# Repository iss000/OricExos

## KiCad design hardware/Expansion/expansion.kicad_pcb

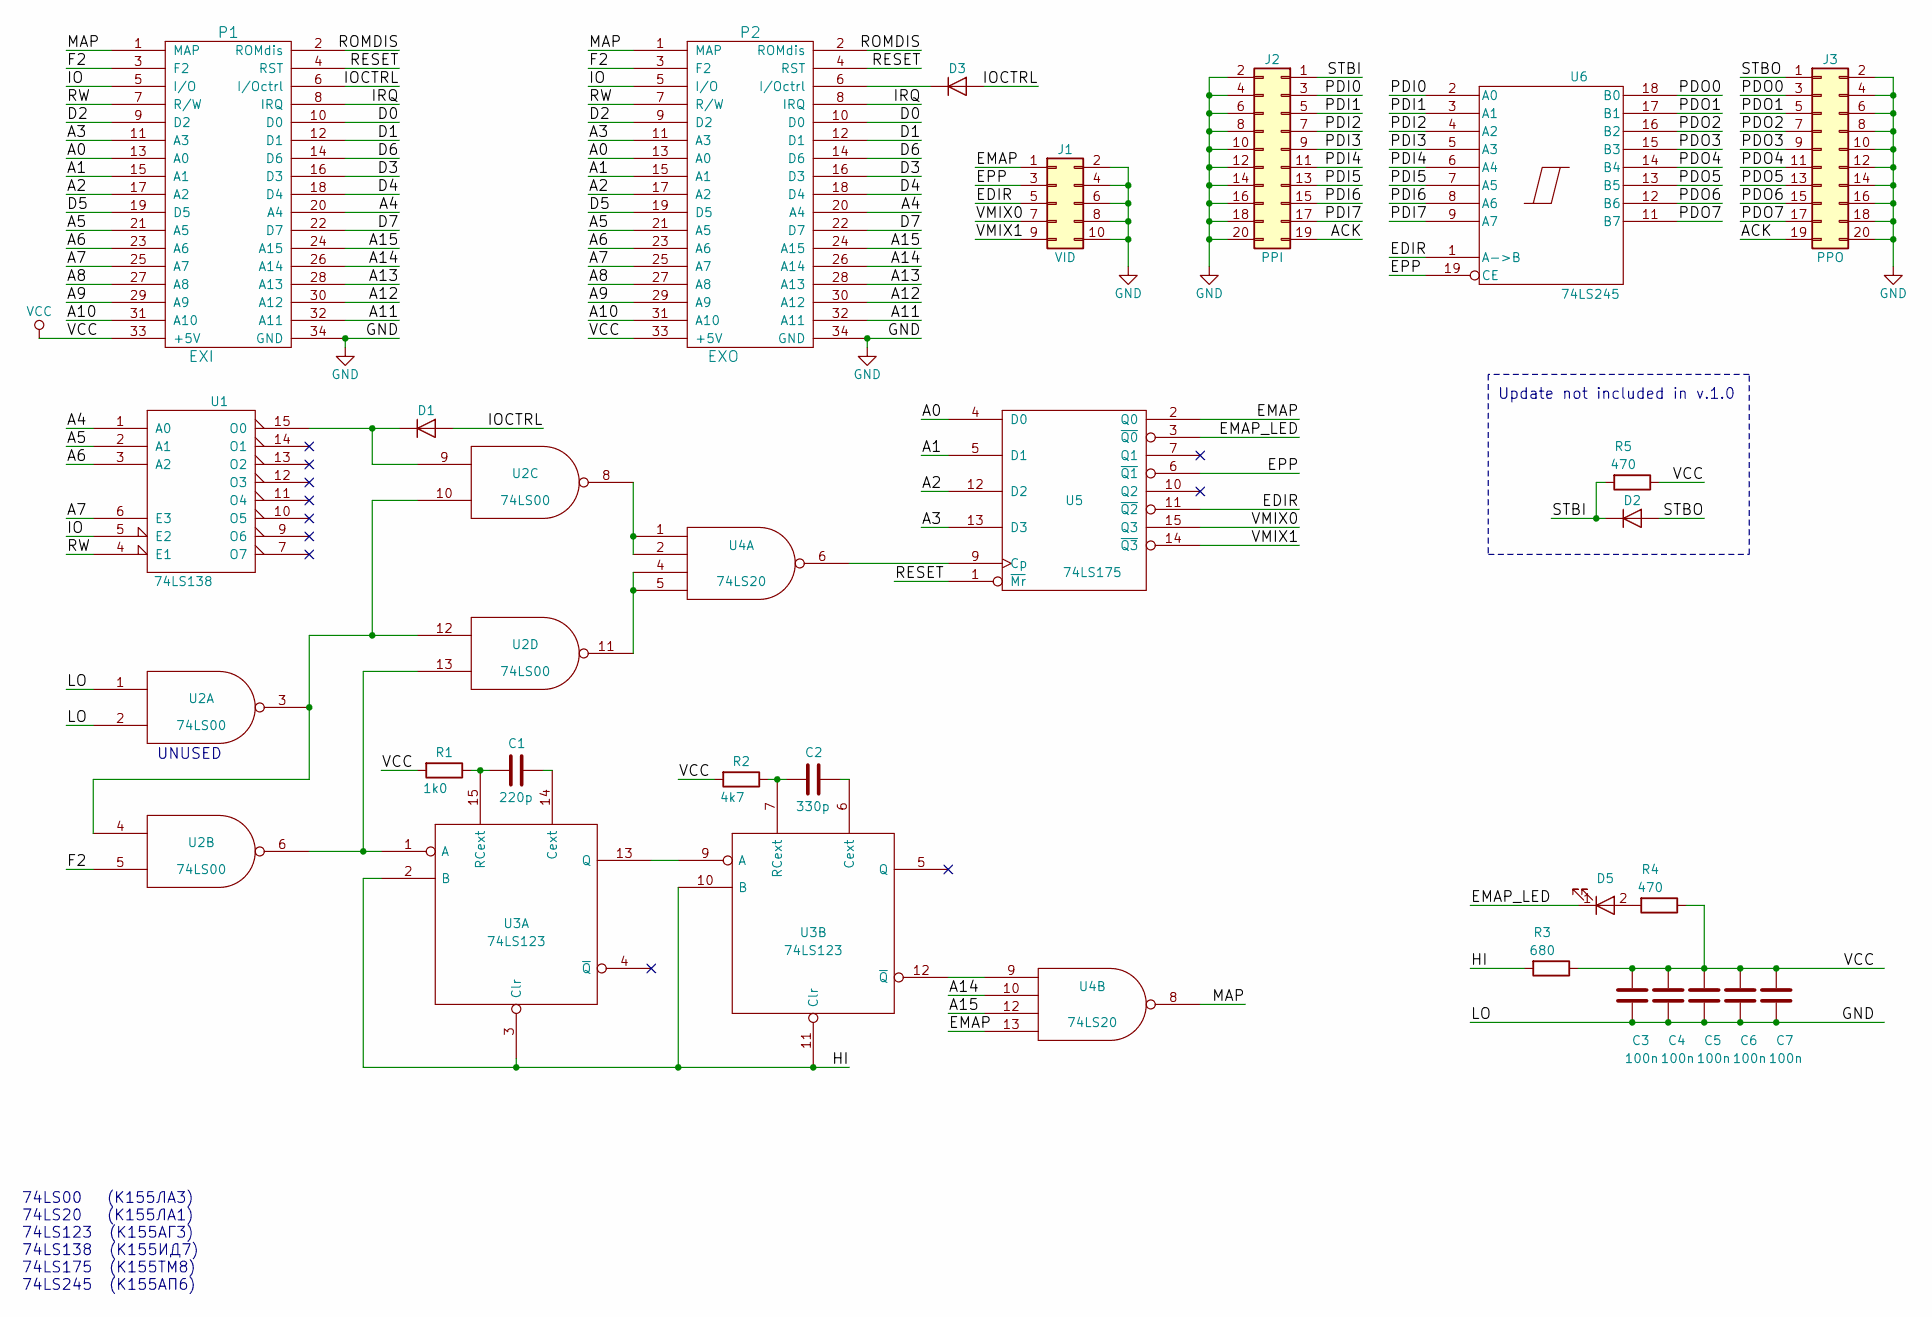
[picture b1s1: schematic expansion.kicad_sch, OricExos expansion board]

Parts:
C1: 220p; C_Disc_D5.0mm_W2.5mm_P2.50mm
C2: 330p; C_Disc_D5.0mm_W2.5mm_P2.50mm
C3, C4, C5, C6, C7: 100n; C_Disc_D5.0mm_W2.5mm_P2.50mm
D1, D2, D3: D; D_A-405_P7.62mm_Horizontal
D5: LED; LED_D3.0mm
J1: VID; Pin_Header_Angled_2x05_Pitch2.54mm
J2: PPI; CONN_EDGE_20
J3: PPO; Multicomp_MC9A12-2034_2x10x2.54mm_Straight
P1: EXI; CONN_EDGE_34
P2: EXO; Multicomp_MC9A12-3434_2x17x2.54mm_Straight
R1: 1k0; R_Axial_DIN0204_L3.6mm_D1.6mm_P7.62mm_Horizontal
R2: 4k7; R_Axial_DIN0204_L3.6mm_D1.6mm_P7.62mm_Horizontal
R3: 680; R_Axial_DIN0204_L3.6mm_D1.6mm_P7.62mm_Horizontal
R4, R5: 470; R_Axial_DIN0204_L3.6mm_D1.6mm_P7.62mm_Horizontal
U1: 74LS138; DIP-16_W7.62mm_Socket_LongPads
U2: 74LS00; DIP-14_W7.62mm_Socket_LongPads
U3: 74LS123; DIP-16_W7.62mm_Socket_LongPads
U4: 74LS20; DIP-14_W7.62mm_Socket_LongPads
U5: 74LS175; DIP-16_W7.62mm_Socket_LongPads
U6: 74LS245; DIP-20_W7.62mm_Socket_LongPads

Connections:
/A0: P1.13 (A0), P2.13 (A0), U5.4 (D0)
/A1: P1.15 (A1), P2.15 (A1), U5.5 (D1)
/A2: P1.17 (A2), P2.17 (A2), U5.12 (D2)
/A3: P1.11 (A3), P2.11 (A3), U5.13 (D3)
/A4: P1.20 (A4), P2.20 (A4), U1.1 (A0)
/A5: P1.21 (A5), P2.21 (A5), U1.2 (A1)
/A6: P1.23 (A6), P2.23 (A6), U1.3 (A2)
/A7: P1.25 (A7), P2.25 (A7), U1.6 (E3)
/A8: P1.27 (A8), P2.27 (A8)
/A9: P1.29 (A9), P2.29 (A9)
/A10: P1.31 (A10), P2.31 (A10)
/A11: P1.32 (A11), P2.32 (A11)
/A12: P1.30 (A12), P2.30 (A12)
/A13: P1.28 (A13), P2.28 (A13)
/A14: P1.26 (A14), P2.26 (A14), U4.10
/A15: P1.24 (A15), P2.24 (A15), U4.12
/ACK: J2.19, J3.19
/D0: P1.10 (D0), P2.10 (D0)
/D1: P1.12 (D1), P2.12 (D1)
/D2: P1.9 (D2), P2.9 (D2)
/D3: P1.16 (D3), P2.16 (D3)
/D4: P1.18 (D4), P2.18 (D4)
/D5: P1.19 (D5), P2.19 (D5)
/D6: P1.14 (D6), P2.14 (D6)
/D7: P1.22 (D7), P2.22 (D7)
/EDIR: J1.5, U5.11 (~Q2), U6.1 (A->B)
/EMAP: J1.1, U4.13, U5.2 (Q0)
/EMAP_LED: D5.1 (K), U5.3 (~Q0)
/EPP: J1.3, U5.6 (~Q1), U6.19 (CE)
/F2: P1.3 (F2), P2.3 (F2), U2.5
/HI: R3.2, U3.2 (B), U3.3 (Clr), U3.10 (B), U3.11 (Clr)
/IO: P1.5 (I/O), P2.5 (I/O), U1.5 (E2)
/IOCTRL: D1.2 (A), D3.2 (A), P1.6 (I/Octrl)
/IRQ: P1.8 (IRQ), P2.8 (IRQ)
/MAP: P1.1 (MAP), P2.1 (MAP), U4.8
/PDI0: J2.3, U6.2 (A0)
/PDI1: J2.5, U6.3 (A1)
/PDI2: J2.7, U6.4 (A2)
/PDI3: J2.9, U6.5 (A3)
/PDI4: J2.11, U6.6 (A4)
/PDI5: J2.13, U6.7 (A5)
/PDI6: J2.15, U6.8 (A6)
/PDI7: J2.17, U6.9 (A7)
/PDO0: J3.3, U6.18 (B0)
/PDO1: J3.5, U6.17 (B1)
/PDO2: J3.7, U6.16 (B2)
/PDO3: J3.9, U6.15 (B3)
/PDO4: J3.11, U6.14 (B4)
/PDO5: J3.13, U6.13 (B5)
/PDO6: J3.15, U6.12 (B6)
/PDO7: J3.17, U6.11 (B7)
/RESET: P1.4 (RST), P2.4 (RST), U5.1 (~Mr)
/ROMDIS: P1.2 (ROMdis), P2.2 (ROMdis)
/RW: P1.7 (R/W), P2.7 (R/W), U1.4 (E1)
/STBI: D2.1 (K), J2.1, R5.2
/STBO: D2.2 (A), J3.1
/VMIX0: J1.7, U5.15 (Q3)
/VMIX1: J1.9, U5.14 (~Q3)
GND: C3.1, C4.1, C5.1, C6.1, C7.1, J1.2, J1.4, J1.6, J1.8, J1.10, J2.2, J2.4, J2.6, J2.8, J2.10, J2.12, J2.14, J2.16, J2.18, J2.20, J3.2, J3.4, J3.6, J3.8, J3.10, J3.12, J3.14, J3.16, J3.18, J3.20, P1.34 (GND), P2.34 (GND), U1.8 (GND), U2.1, U2.2, U2.7 (GND), U3.8 (GND), U4.7 (GND), U5.8 (GND), U6.10 (GND)
unnamed: C1.1, U3.14 (Cext)
unnamed: C1.2, R1.1, U3.15 (RCext)
unnamed: C2.1, U3.6 (Cext)
unnamed: C2.2, R2.1, U3.7 (RCext)
unnamed: D1.1 (K), U1.15 (O0), U2.9
unnamed: D3.1 (K), P2.6 (I/Octrl)
unnamed: D5.2 (A), R4.2
unnamed: U2.8, U4.1, U4.2
unnamed: U2.3, U2.4, U2.10, U2.12
unnamed: U2.11, U4.4, U4.5
unnamed: U2.6, U2.13, U3.1 (A)
unnamed: U3.12 (~Q), U4.9
unnamed: U3.9 (A), U3.13 (Q)
unnamed: U4.6, U5.9 (Cp)
VCC: C3.2, C4.2, C5.2, C6.2, C7.2, P1.33 (+5V), P2.33 (+5V), R1.2, R2.2, R3.1, R4.1, R5.1, U1.16 (VCC), U2.14 (VCC), U3.16 (VCC), U4.14 (VCC), U5.16 (VCC), U6.20 (VCC)

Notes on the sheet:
74LS00 (К155ЛА3) 74LS20 (К155ЛА1) 74LS123 (К155АГ3) 74LS138 (К155ИД7) 74LS175 (К155ТМ8) 74LS245 (К155АП6)
UNUSED
Update not included in v.1.0

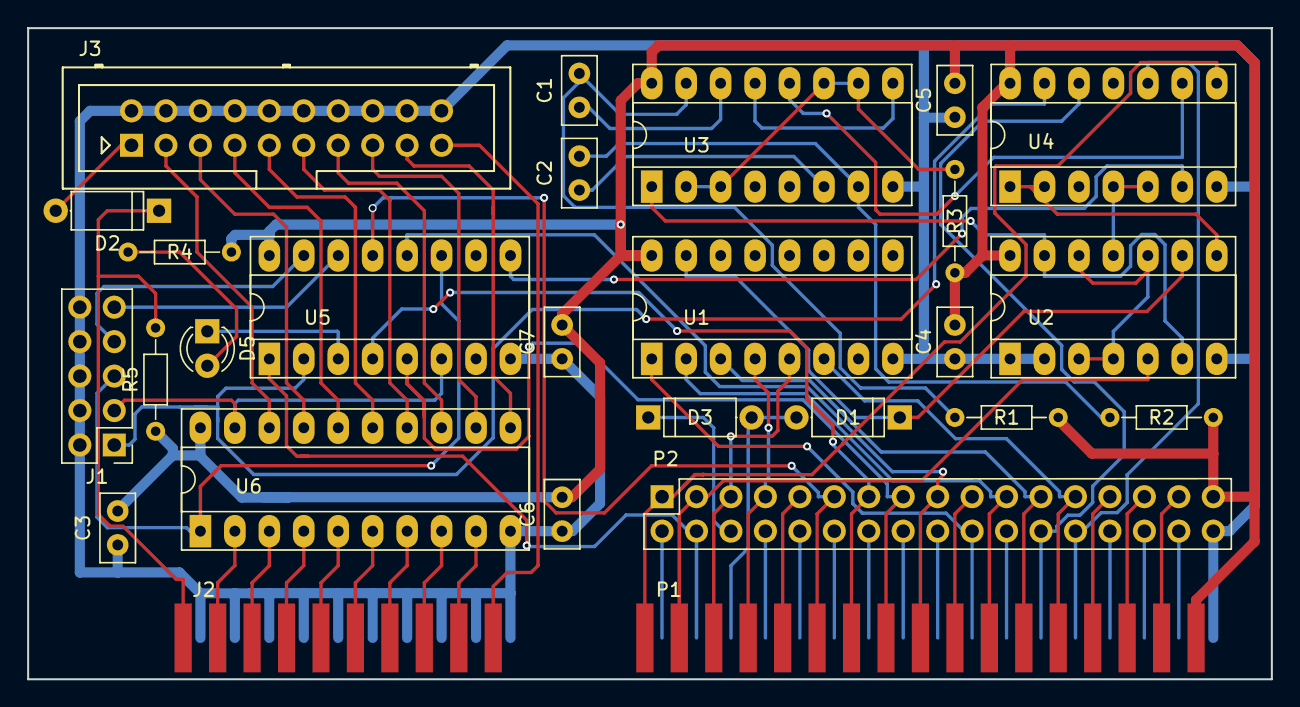
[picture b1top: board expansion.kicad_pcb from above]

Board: 2 copper layers, 91.7 x 48.0 mm, 27 parts (0 on the bottom side), 74 nets.

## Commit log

2018-09-15 VSync
2018-09-21 adding ROM files for master and slave
2018-09-22 update in roms
2018-09-23 building Master Oric
2018-09-23 add Master schematics
2018-09-28 update slave ROMs
2018-10-08 improved slave roms
2018-10-09 adding software (first tests)
2018-10-09 adding test:circles
2018-10-09 adding test:circles (fix)
2018-10-10 adding test:morebars
2018-10-25 update test:circles
2018-10-28 adding test:tesseract
2018-10-28 update test:tesseract
2018-11-04 update tests
2018-11-05 tests restructure
2018-11-10 tests
2018-11-11 tests:tape-xfer tryouts
2018-11-14 update roms
2018-11-14 update:roms
2018-12-03 adding expansion hw
2018-12-13 update:expansion
2018-12-16 Revert "update:expansion"
    This reverts commit fc7daa09fcab310e52193976a9df76314ecc8e0b.
2018-12-16 revert:expansion
2019-11-04 fix: shut function (#145)
2019-12-04 updating emulator
2021-02-10 fix: BD500 support
2021-02-13 fix: BD500 support+
2021-02-13 tag 1.2.2

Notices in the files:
hardware/Expansion/expansion.kicad_pcb:
copyright © 2018 iss
